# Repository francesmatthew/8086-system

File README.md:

# 8086-system
8086-based system, designed in KiCAD

3D Render of PCB

PCB Overview (fill zones not shown)

Root Sheet

8086 Processor and Bus Demultiplexing Logic

28F010 CMOS Flash

CY7C199 SRAM

8284A Clock Generator

PAL16L8 I/O Address Decoding

8259 Interrupt Controller

8254 Counter

8279 Keyboard

16550 UART Interface

8255 Programmable Peripheral Interface 1

8255 Programmable Peripheral Interface 2

8255 Programmable Peripheral Interface 3

LCD, 7-Segment Displays, LEDs, DIP Switches

Bus Headers, Power Connections

Front Copper Layer

Inner Copper Layer 1

Inner Copper Layer 2

Back Copper Layer

This repository is for submission as the final project for Systems Design and Programming at the University of Maryland, Baltimore County under instruction of William Smith

Unauthorized copying of this project is considered a violation of university academic integrity policy

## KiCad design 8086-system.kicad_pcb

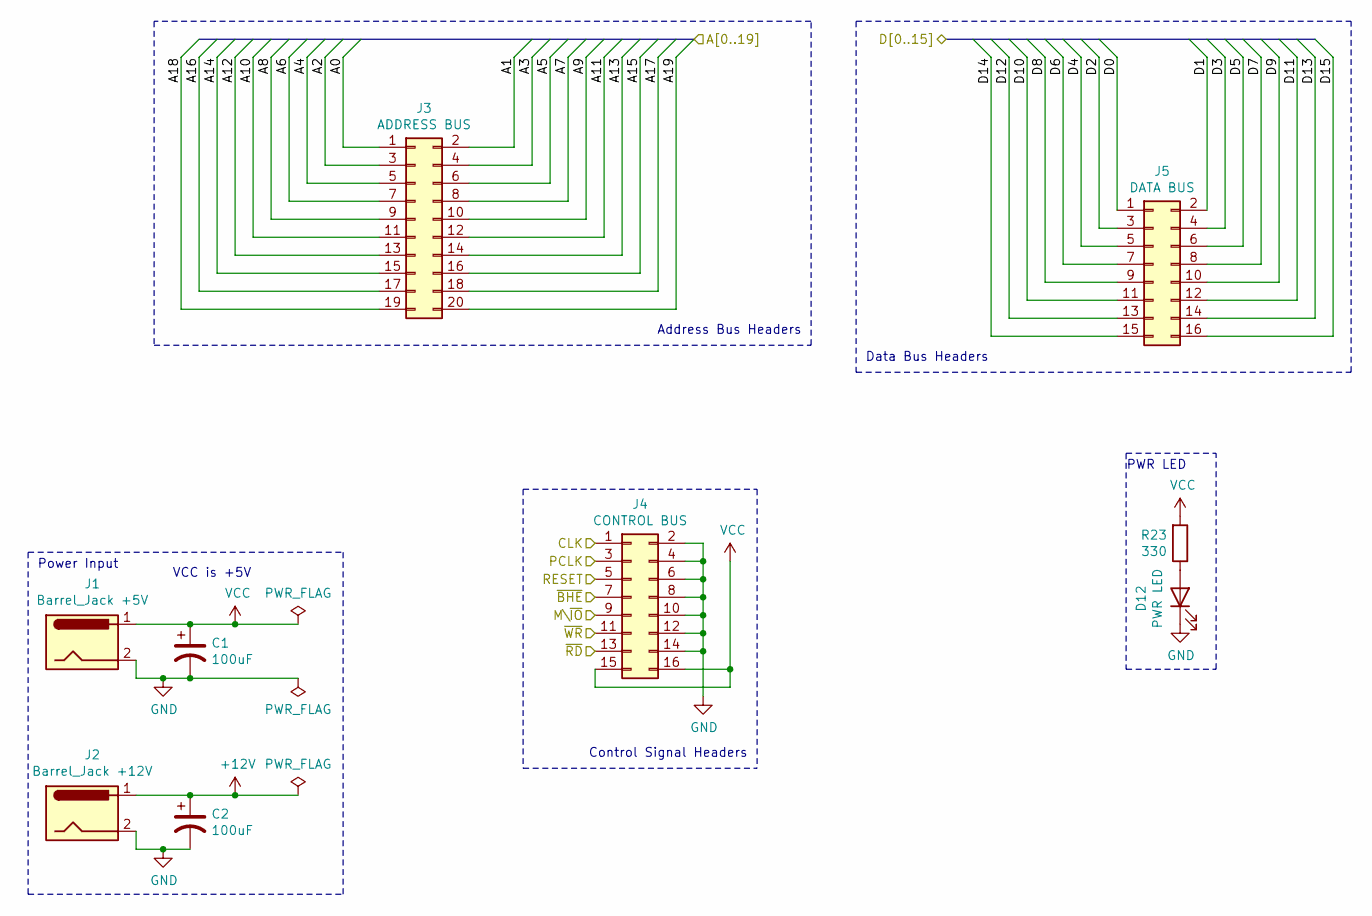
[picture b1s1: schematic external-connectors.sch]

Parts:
C1, C2: 100uF; C_Radial_D6.3mm_H5.0mm_P2.50mm
D12: PWR LED; LED_D5.0mm
J1: Barrel_Jack +5V; BarrelJack_Horizontal
J2: Barrel_Jack +12V; BarrelJack_Horizontal
J3: ADDRESS BUS; PinHeader_2x10_P2.54mm_Vertical
J4: CONTROL BUS; PinHeader_2x08_P2.54mm_Vertical
J5: DATA BUS; PinHeader_2x08_P2.54mm_Vertical
R23: 330; R_Axial_DIN0207_L6.3mm_D2.5mm_P10.16mm_Horizontal

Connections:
+12V: C2.1, J2.1; also elsewhere on the board
/8086-processor/A0: J3.1; also elsewhere on the board
/8086-processor/A1: J3.2; also elsewhere on the board
/8086-processor/A2: J3.3; also elsewhere on the board
/8086-processor/A3: J3.4; also elsewhere on the board
/8086-processor/A4: J3.5; also elsewhere on the board
/8086-processor/A5: J3.6; also elsewhere on the board
/8086-processor/A6: J3.7; also elsewhere on the board
/8086-processor/A7: J3.8; also elsewhere on the board
/8086-processor/A8: J3.9; also elsewhere on the board
/8086-processor/A9: J3.10; also elsewhere on the board
/8086-processor/A10: J3.11; also elsewhere on the board
/8086-processor/A11: J3.12; also elsewhere on the board
/8086-processor/A12: J3.13; also elsewhere on the board
/8086-processor/A13: J3.14; also elsewhere on the board
/8086-processor/A14: J3.15; also elsewhere on the board
/8086-processor/A15: J3.16; also elsewhere on the board
/8086-processor/A16: J3.17; also elsewhere on the board
/8086-processor/A17: J3.18; also elsewhere on the board
/8086-processor/A18: J3.19; also elsewhere on the board
/8086-processor/A19: J3.20; also elsewhere on the board
/8086-processor/D0: J5.1; also elsewhere on the board
/8086-processor/D1: J5.2; also elsewhere on the board
/8086-processor/D2: J5.3; also elsewhere on the board
/8086-processor/D3: J5.4; also elsewhere on the board
/8086-processor/D4: J5.5; also elsewhere on the board
/8086-processor/D5: J5.6; also elsewhere on the board
/8086-processor/D6: J5.7; also elsewhere on the board
/8086-processor/D7: J5.8; also elsewhere on the board
/8086-processor/D8: J5.9; also elsewhere on the board
/8086-processor/D9: J5.10; also elsewhere on the board
/8086-processor/D10: J5.11; also elsewhere on the board
/8086-processor/D11: J5.12; also elsewhere on the board
/8086-processor/D12: J5.13; also elsewhere on the board
/8086-processor/D13: J5.14; also elsewhere on the board
/8086-processor/D14: J5.15; also elsewhere on the board
/8086-processor/D15: J5.16; also elsewhere on the board
/CLK: J4.1; also elsewhere on the board
/M\~IO: J4.9; also elsewhere on the board
/PCLK: J4.3; also elsewhere on the board
/RESET: J4.5; also elsewhere on the board
/~BHE: J4.7; also elsewhere on the board
/~RD: J4.13; also elsewhere on the board
/~WR: J4.11; also elsewhere on the board
GND: C1.2, C2.2, D12.1 (K), J1.2, J2.2, J4.2, J4.4, J4.6, J4.8, J4.10, J4.12, J4.14; also elsewhere on the board
unnamed: D12.2 (A), R23.1
VCC: C1.1, J1.1, J4.15, J4.16, R23.2; also elsewhere on the board

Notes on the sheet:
Data Bus Headers
Address Bus Headers
Power Input
VCC is +5V
Control Signal Headers
PWR LED

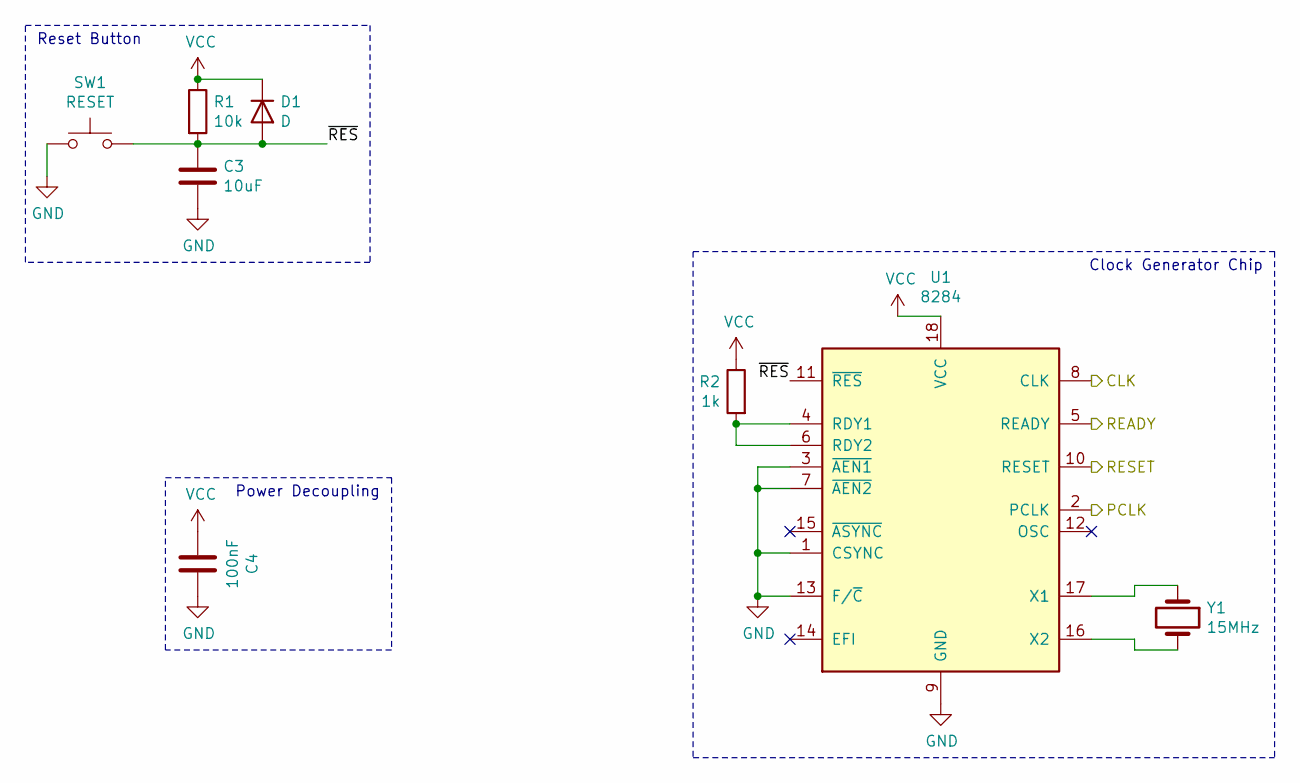
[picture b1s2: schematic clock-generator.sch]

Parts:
C3: 10uF; C_Rect_L4.6mm_W3.8mm_P2.50mm_MKS02_FKP02
C4: 100nF; C_Rect_L4.0mm_W2.5mm_P2.50mm
D1: D; D_DO-35_SOD27_P7.62mm_Horizontal
R1: 10k; R_Axial_DIN0207_L6.3mm_D2.5mm_P10.16mm_Horizontal
R2: 1k; R_Axial_DIN0207_L6.3mm_D2.5mm_P10.16mm_Horizontal
SW1: RESET; SW_Cherry_MX_1.00u_PCB
U1: 8284; DIP-18_W7.62mm
Y1: 15MHz; Crystal_HC49-4H_Vertical

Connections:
/CLK: U1.8 (CLK); also elsewhere on the board
/PCLK: U1.2 (PCLK); also elsewhere on the board
/READY: U1.5 (READY); also elsewhere on the board
/RESET: U1.10 (RESET); also elsewhere on the board
/clock-generator/~RES: C3.1, D1.2 (A), R1.2, SW1.2, U1.11 (~RES~)
GND: C3.2, C4.2, SW1.1, U1.1 (CSYNC), U1.3 (~AEN1~), U1.7 (~AEN2~), U1.9 (GND), U1.13 (F/~C~); also elsewhere on the board
unnamed: R2.2, U1.4 (RDY1), U1.6 (RDY2)
unnamed: U1.16 (X2), Y1.2
unnamed: U1.17 (X1), Y1.1
VCC: C4.1, D1.1 (K), R1.1, R2.1, U1.18 (VCC); also elsewhere on the board

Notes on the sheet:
Clock Generator Chip
Power Decoupling
Reset Button

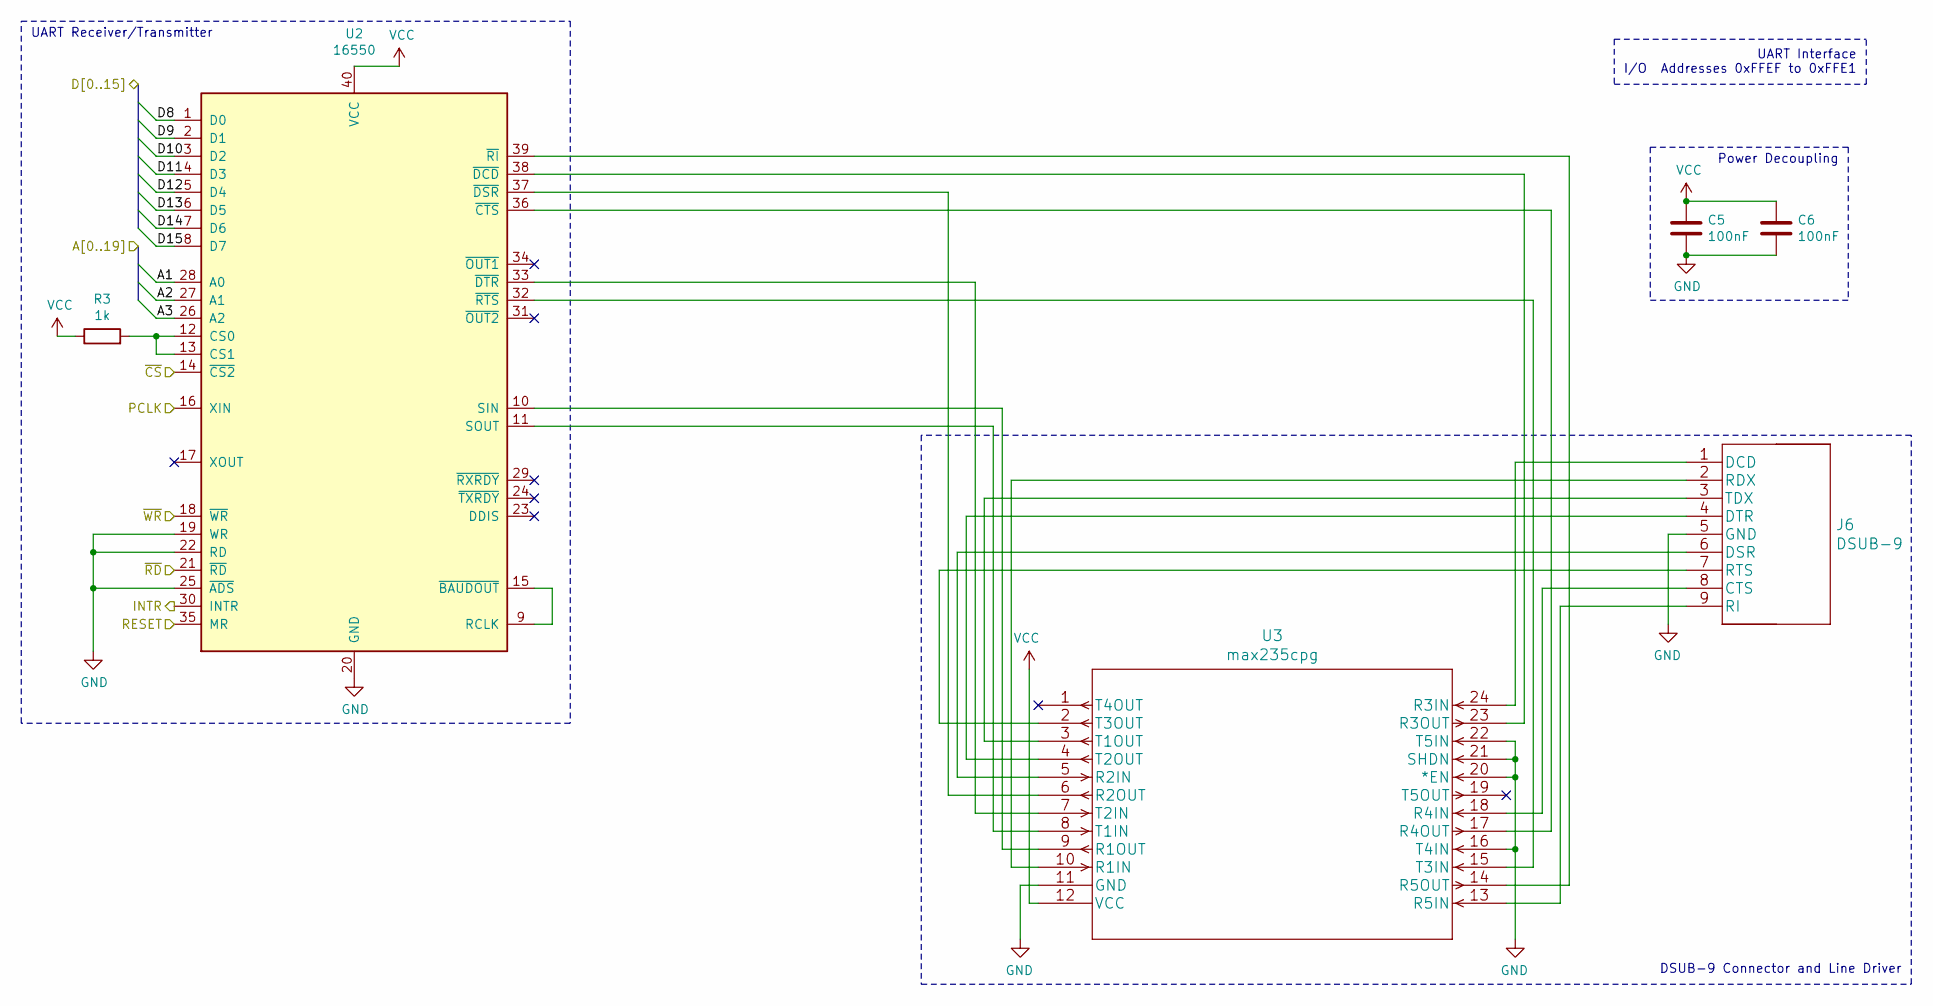
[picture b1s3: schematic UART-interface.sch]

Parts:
C5, C6: 100nF; C_Rect_L4.0mm_W2.5mm_P2.50mm
J6: DSUB-9
R3: 1k; R_Axial_DIN0207_L6.3mm_D2.5mm_P10.16mm_Horizontal
U2: 16550; DIP-40_W15.24mm
U3: max235cpg

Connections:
/8086-processor/A1: U2.28 (A0); also elsewhere on the board
/8086-processor/A2: U2.27 (A1); also elsewhere on the board
/8086-processor/A3: U2.26 (A2); also elsewhere on the board
/8086-processor/D8: U2.1 (D0); also elsewhere on the board
/8086-processor/D9: U2.2 (D1); also elsewhere on the board
/8086-processor/D10: U2.3 (D2); also elsewhere on the board
/8086-processor/D11: U2.4 (D3); also elsewhere on the board
/8086-processor/D12: U2.5 (D4); also elsewhere on the board
/8086-processor/D13: U2.6 (D5); also elsewhere on the board
/8086-processor/D14: U2.7 (D6); also elsewhere on the board
/8086-processor/D15: U2.8 (D7); also elsewhere on the board
/PCLK: U2.16 (XIN); also elsewhere on the board
/RESET: U2.35 (MR); also elsewhere on the board
/UART_INTR: U2.30 (INTR); also elsewhere on the board
/~CS_UART: U2.14 (~CS2~); also elsewhere on the board
/~RD: U2.21 (~RD~); also elsewhere on the board
/~WR: U2.18 (~WR~); also elsewhere on the board
GND: C5.2, C6.2, J6.5 (GND), U2.19 (WR), U2.20 (GND), U2.22 (RD), U2.25 (~ADS~), U3.11 (GND), U3.16 (T4IN), U3.20 (*EN), U3.21 (SHDN), U3.22 (T5IN); also elsewhere on the board
unnamed: J6.1 (DCD), U3.24 (R3IN)
unnamed: J6.2 (RDX), U3.10 (R1IN)
unnamed: J6.3 (TDX), U3.3 (T1OUT)
unnamed: J6.4 (DTR), U3.4 (T2OUT)
unnamed: J6.6 (DSR), U3.5 (R2IN)
unnamed: J6.7 (RTS), U3.2 (T3OUT)
unnamed: J6.8 (CTS), U3.18 (R4IN)
unnamed: J6.9 (RI), U3.13 (R5IN)
unnamed: R3.2, U2.12 (CS0), U2.13 (CS1)
unnamed: U2.10 (SIN), U3.9 (R1OUT)
unnamed: U2.11 (SOUT), U3.8 (T1IN)
unnamed: U2.9 (RCLK), U2.15 (~BAUDOUT~)
unnamed: U2.32 (~RTS~), U3.15 (T3IN)
unnamed: U2.33 (~DTR~), U3.7 (T2IN)
unnamed: U2.36 (~CTS~), U3.17 (R4OUT)
unnamed: U2.37 (~DSR~), U3.6 (R2OUT)
unnamed: U2.38 (~DCD~), U3.23 (R3OUT)
unnamed: U2.39 (~RI~), U3.14 (R5OUT)
VCC: C5.1, C6.1, R3.1, U2.40 (VCC), U3.12 (VCC); also elsewhere on the board

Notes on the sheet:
UART Interface I/O Addresses 0xFFEF to 0xFFE1
UART Receiver/Transmitter
Power Decoupling
DSUB-9 Connector and Line Driver

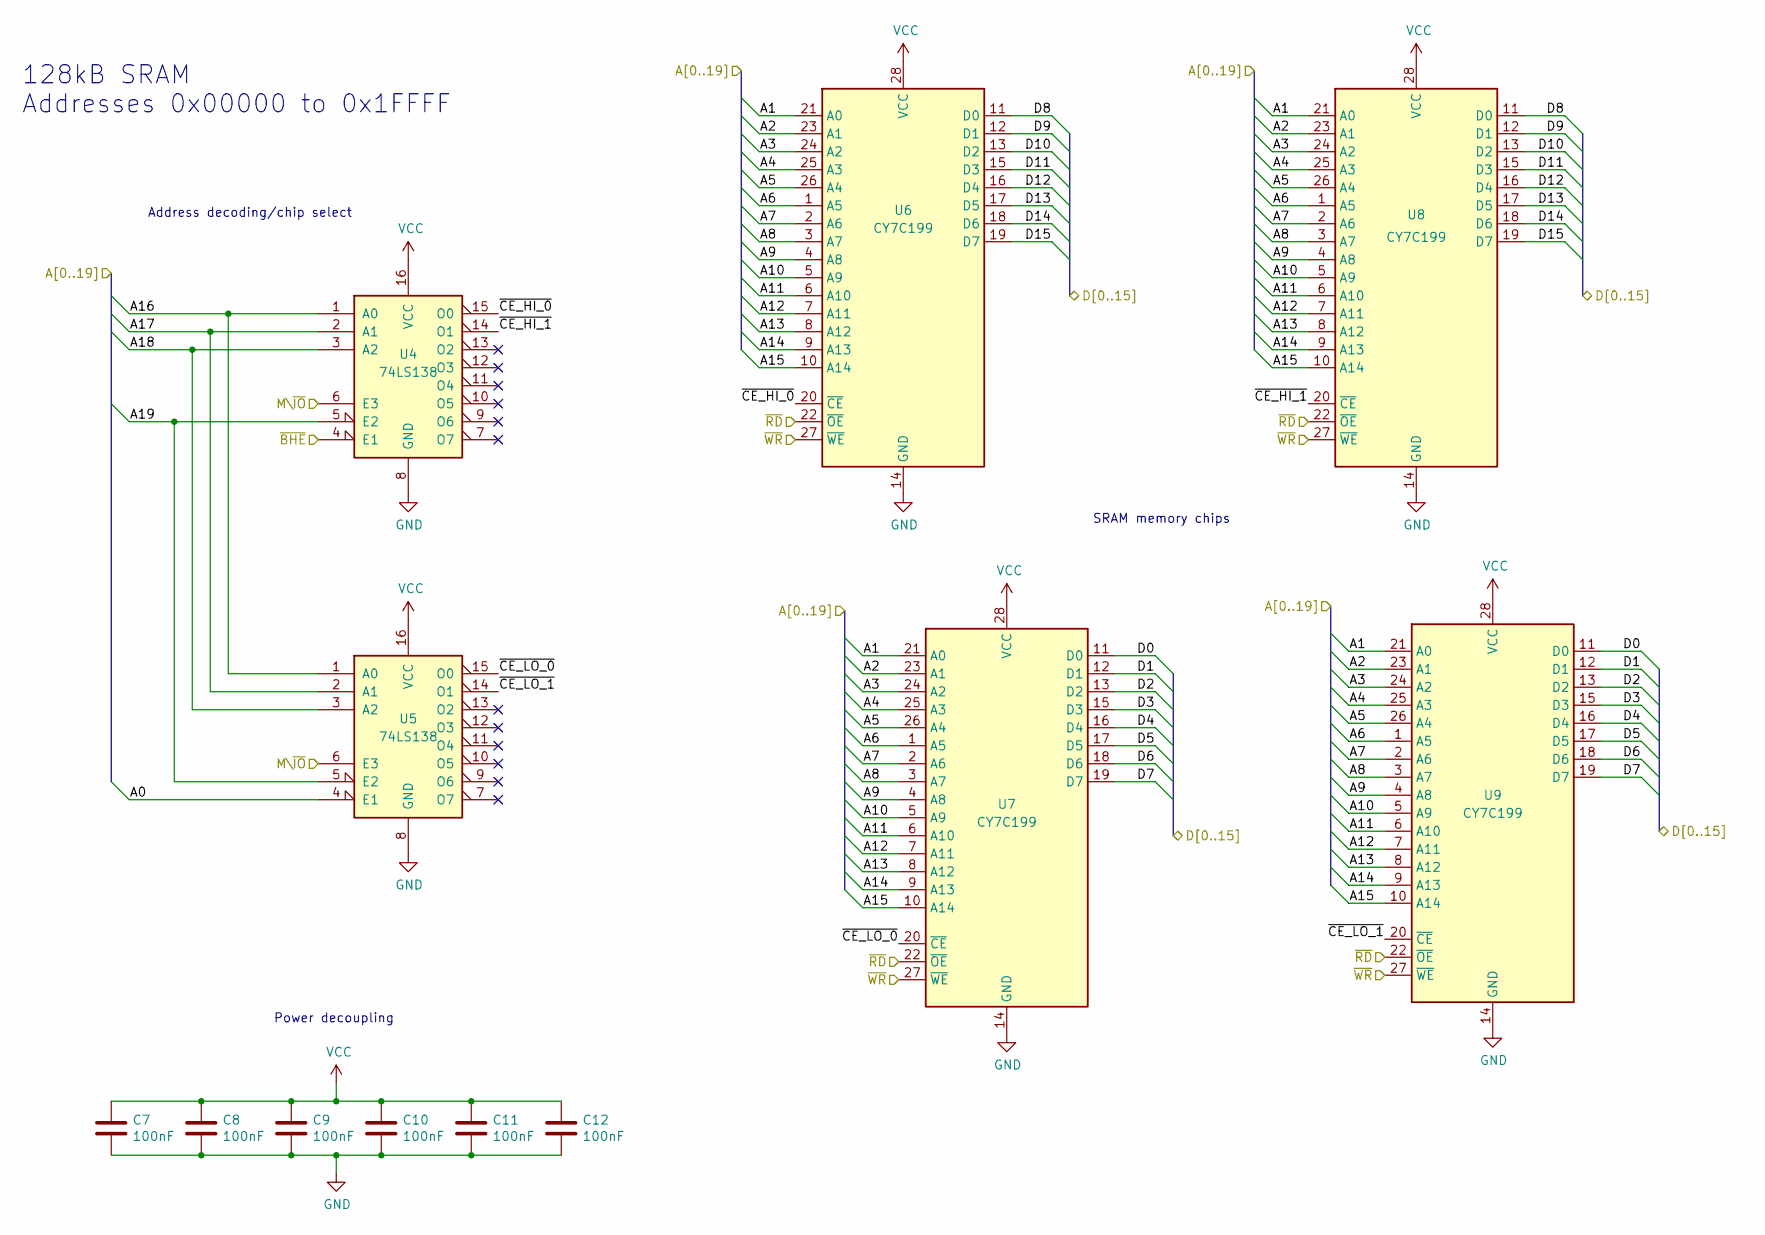
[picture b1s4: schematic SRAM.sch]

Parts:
C7, C8, C9, C10, C11, C12: 100nF; C_Rect_L4.0mm_W2.5mm_P2.50mm
U4, U5: 74LS138; DIP-16_W7.62mm
U6, U7, U8, U9: CY7C199; DIP-28_W7.62mm

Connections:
/8086-processor/A0: U5.4 (E1); also elsewhere on the board
/8086-processor/A1: U6.21 (A0), U7.21 (A0), U8.21 (A0), U9.21 (A0); also elsewhere on the board
/8086-processor/A2: U6.23 (A1), U7.23 (A1), U8.23 (A1), U9.23 (A1); also elsewhere on the board
/8086-processor/A3: U6.24 (A2), U7.24 (A2), U8.24 (A2), U9.24 (A2); also elsewhere on the board
/8086-processor/A4: U6.25 (A3), U7.25 (A3), U8.25 (A3), U9.25 (A3); also elsewhere on the board
/8086-processor/A5: U6.26 (A4), U7.26 (A4), U8.26 (A4), U9.26 (A4); also elsewhere on the board
/8086-processor/A6: U6.1 (A5), U7.1 (A5), U8.1 (A5), U9.1 (A5); also elsewhere on the board
/8086-processor/A7: U6.2 (A6), U7.2 (A6), U8.2 (A6), U9.2 (A6); also elsewhere on the board
/8086-processor/A8: U6.3 (A7), U7.3 (A7), U8.3 (A7), U9.3 (A7); also elsewhere on the board
/8086-processor/A9: U6.4 (A8), U7.4 (A8), U8.4 (A8), U9.4 (A8); also elsewhere on the board
/8086-processor/A10: U6.5 (A9), U7.5 (A9), U8.5 (A9), U9.5 (A9); also elsewhere on the board
/8086-processor/A11: U6.6 (A10), U7.6 (A10), U8.6 (A10), U9.6 (A10); also elsewhere on the board
/8086-processor/A12: U6.7 (A11), U7.7 (A11), U8.7 (A11), U9.7 (A11); also elsewhere on the board
/8086-processor/A13: U6.8 (A12), U7.8 (A12), U8.8 (A12), U9.8 (A12); also elsewhere on the board
/8086-processor/A14: U6.9 (A13), U7.9 (A13), U8.9 (A13), U9.9 (A13); also elsewhere on the board
/8086-processor/A15: U6.10 (A14), U7.10 (A14), U8.10 (A14), U9.10 (A14); also elsewhere on the board
/8086-processor/A16: U4.1 (A0), U5.1 (A0); also elsewhere on the board
/8086-processor/A17: U4.2 (A1), U5.2 (A1); also elsewhere on the board
/8086-processor/A18: U4.3 (A2), U5.3 (A2); also elsewhere on the board
/8086-processor/A19: U4.5 (E2), U5.5 (E2); also elsewhere on the board
/8086-processor/D0: U7.11 (D0), U9.11 (D0); also elsewhere on the board
/8086-processor/D1: U7.12 (D1), U9.12 (D1); also elsewhere on the board
/8086-processor/D2: U7.13 (D2), U9.13 (D2); also elsewhere on the board
/8086-processor/D3: U7.15 (D3), U9.15 (D3); also elsewhere on the board
/8086-processor/D4: U7.16 (D4), U9.16 (D4); also elsewhere on the board
/8086-processor/D5: U7.17 (D5), U9.17 (D5); also elsewhere on the board
/8086-processor/D6: U7.18 (D6), U9.18 (D6); also elsewhere on the board
/8086-processor/D7: U7.19 (D7), U9.19 (D7); also elsewhere on the board
/8086-processor/D8: U6.11 (D0), U8.11 (D0); also elsewhere on the board
/8086-processor/D9: U6.12 (D1), U8.12 (D1); also elsewhere on the board
/8086-processor/D10: U6.13 (D2), U8.13 (D2); also elsewhere on the board
/8086-processor/D11: U6.15 (D3), U8.15 (D3); also elsewhere on the board
/8086-processor/D12: U6.16 (D4), U8.16 (D4); also elsewhere on the board
/8086-processor/D13: U6.17 (D5), U8.17 (D5); also elsewhere on the board
/8086-processor/D14: U6.18 (D6), U8.18 (D6); also elsewhere on the board
/8086-processor/D15: U6.19 (D7), U8.19 (D7); also elsewhere on the board
/M\~IO: U4.6 (E3), U5.6 (E3); also elsewhere on the board
/SRAM/~CE_HI_0: U4.15 (O0), U6.20 (~CE~)
/SRAM/~CE_HI_1: U4.14 (O1), U8.20 (~CE~)
/SRAM/~CE_LO_0: U5.15 (O0), U7.20 (~CE~)
/SRAM/~CE_LO_1: U5.14 (O1), U9.20 (~CE~)
/~BHE: U4.4 (E1); also elsewhere on the board
/~RD: U6.22 (~OE~), U7.22 (~OE~), U8.22 (~OE~), U9.22 (~OE~); also elsewhere on the board
/~WR: U6.27 (~WE~), U7.27 (~WE~), U8.27 (~WE~), U9.27 (~WE~); also elsewhere on the board
GND: C7.2, C8.2, C9.2, C10.2, C11.2, C12.2, U4.8 (GND), U5.8 (GND), U6.14 (GND), U7.14 (GND), U8.14 (GND), U9.14 (GND); also elsewhere on the board
VCC: C7.1, C8.1, C9.1, C10.1, C11.1, C12.1, U4.16 (VCC), U5.16 (VCC), U6.28 (VCC), U7.28 (VCC), U8.28 (VCC), U9.28 (VCC); also elsewhere on the board

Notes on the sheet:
128kB SRAM Addresses 0x00000 to 0x1FFFF
Address decoding/chip select
Power decoupling
SRAM memory chips

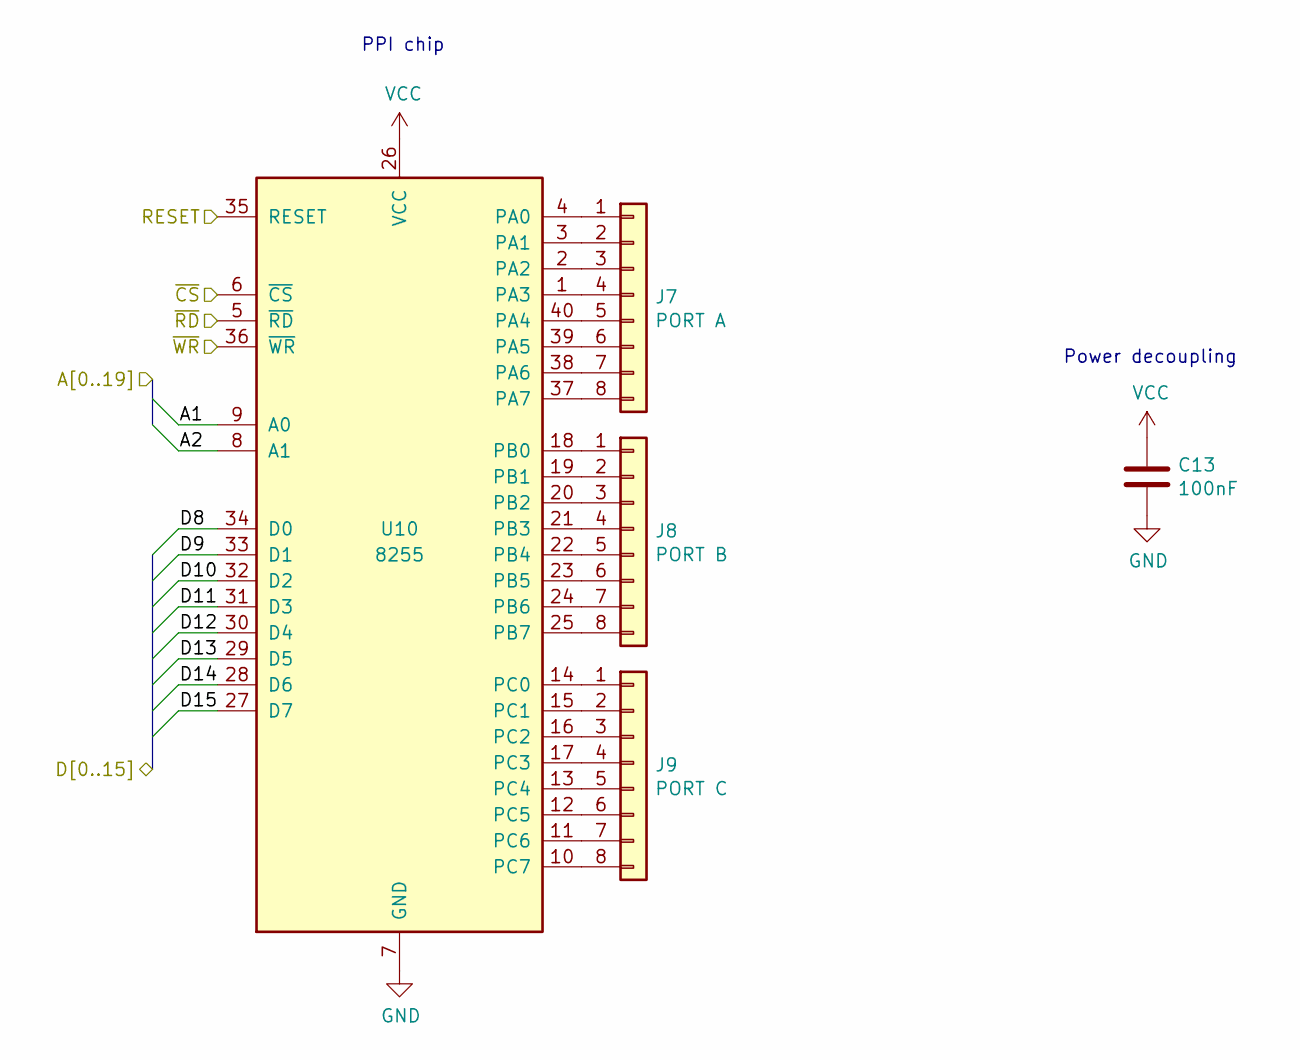
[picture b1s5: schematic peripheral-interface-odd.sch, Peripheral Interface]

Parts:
C13: 100nF; C_Rect_L4.0mm_W2.5mm_P2.50mm
J10: PORT A; PinHeader_1x08_P2.54mm_Vertical
J11: PORT B; PinHeader_1x08_P2.54mm_Vertical
J12: PORT C; PinHeader_1x08_P2.54mm_Vertical
U11: 8255; DIP-40_W15.24mm

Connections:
/8086-processor/A1: U11.9 (A0); also elsewhere on the board
/8086-processor/A2: U11.8 (A1); also elsewhere on the board
/8086-processor/D8: U11.34 (D0); also elsewhere on the board
/8086-processor/D9: U11.33 (D1); also elsewhere on the board
/8086-processor/D10: U11.32 (D2); also elsewhere on the board
/8086-processor/D11: U11.31 (D3); also elsewhere on the board
/8086-processor/D12: U11.30 (D4); also elsewhere on the board
/8086-processor/D13: U11.29 (D5); also elsewhere on the board
/8086-processor/D14: U11.28 (D6); also elsewhere on the board
/8086-processor/D15: U11.27 (D7); also elsewhere on the board
/RESET: U11.35 (RESET); also elsewhere on the board
/~CS_PPI1: U11.6 (~CS~); also elsewhere on the board
/~RD: U11.5 (~RD~); also elsewhere on the board
/~WR: U11.36 (~WR~); also elsewhere on the board
GND: C13.2, U11.7 (GND); also elsewhere on the board
unnamed: J10.1, U11.4 (PA0)
unnamed: J10.2, U11.3 (PA1)
unnamed: J10.3, U11.2 (PA2)
unnamed: J10.4, U11.1 (PA3)
unnamed: J10.5, U11.40 (PA4)
unnamed: J10.6, U11.39 (PA5)
unnamed: J10.7, U11.38 (PA6)
unnamed: J10.8, U11.37 (PA7)
unnamed: J11.1, U11.18 (PB0)
unnamed: J11.2, U11.19 (PB1)
unnamed: J11.3, U11.20 (PB2)
unnamed: J11.4, U11.21 (PB3)
unnamed: J11.5, U11.22 (PB4)
unnamed: J11.6, U11.23 (PB5)
unnamed: J11.7, U11.24 (PB6)
unnamed: J11.8, U11.25 (PB7)
unnamed: J12.1, U11.14 (PC0)
unnamed: J12.2, U11.15 (PC1)
unnamed: J12.3, U11.16 (PC2)
unnamed: J12.4, U11.17 (PC3)
unnamed: J12.5, U11.13 (PC4)
unnamed: J12.6, U11.12 (PC5)
unnamed: J12.7, U11.11 (PC6)
unnamed: J12.8, U11.10 (PC7)
VCC: C13.1, U11.26 (VCC); also elsewhere on the board

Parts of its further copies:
C14: 100nF; C_Rect_L4.0mm_W2.5mm_P2.50mm
J7: PORT A; PinHeader_1x08_P2.54mm_Vertical
J8: PORT B; PinHeader_1x08_P2.54mm_Vertical
J9: PORT C; PinHeader_1x08_P2.54mm_Vertical
U10: 8255; DIP-40_W15.24mm

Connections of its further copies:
/8086-processor/A1: U10.9 (A0); also elsewhere on the board
/8086-processor/A2: U10.8 (A1); also elsewhere on the board
/8086-processor/D8: U10.34 (D0); also elsewhere on the board
/8086-processor/D9: U10.33 (D1); also elsewhere on the board
/8086-processor/D10: U10.32 (D2); also elsewhere on the board
/8086-processor/D11: U10.31 (D3); also elsewhere on the board
/8086-processor/D12: U10.30 (D4); also elsewhere on the board
/8086-processor/D13: U10.29 (D5); also elsewhere on the board
/8086-processor/D14: U10.28 (D6); also elsewhere on the board
/8086-processor/D15: U10.27 (D7); also elsewhere on the board
/RESET: U10.35 (RESET); also elsewhere on the board
/~CS_PPI3: U10.6 (~CS~); also elsewhere on the board
/~RD: U10.5 (~RD~); also elsewhere on the board
/~WR: U10.36 (~WR~); also elsewhere on the board
GND: C14.2, U10.7 (GND); also elsewhere on the board
unnamed: J7.1, U10.4 (PA0)
unnamed: J7.2, U10.3 (PA1)
unnamed: J7.3, U10.2 (PA2)
unnamed: J7.4, U10.1 (PA3)
unnamed: J7.5, U10.40 (PA4)
unnamed: J7.6, U10.39 (PA5)
unnamed: J7.7, U10.38 (PA6)
unnamed: J7.8, U10.37 (PA7)
unnamed: J8.1, U10.18 (PB0)
unnamed: J8.2, U10.19 (PB1)
unnamed: J8.3, U10.20 (PB2)
unnamed: J8.4, U10.21 (PB3)
unnamed: J8.5, U10.22 (PB4)
unnamed: J8.6, U10.23 (PB5)
unnamed: J8.7, U10.24 (PB6)
unnamed: J8.8, U10.25 (PB7)
unnamed: J9.1, U10.14 (PC0)
unnamed: J9.2, U10.15 (PC1)
unnamed: J9.3, U10.16 (PC2)
unnamed: J9.4, U10.17 (PC3)
unnamed: J9.5, U10.13 (PC4)
unnamed: J9.6, U10.12 (PC5)
unnamed: J9.7, U10.11 (PC6)
unnamed: J9.8, U10.10 (PC7)
VCC: C14.1, U10.26 (VCC); also elsewhere on the board

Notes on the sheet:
PPI chip
Power decoupling

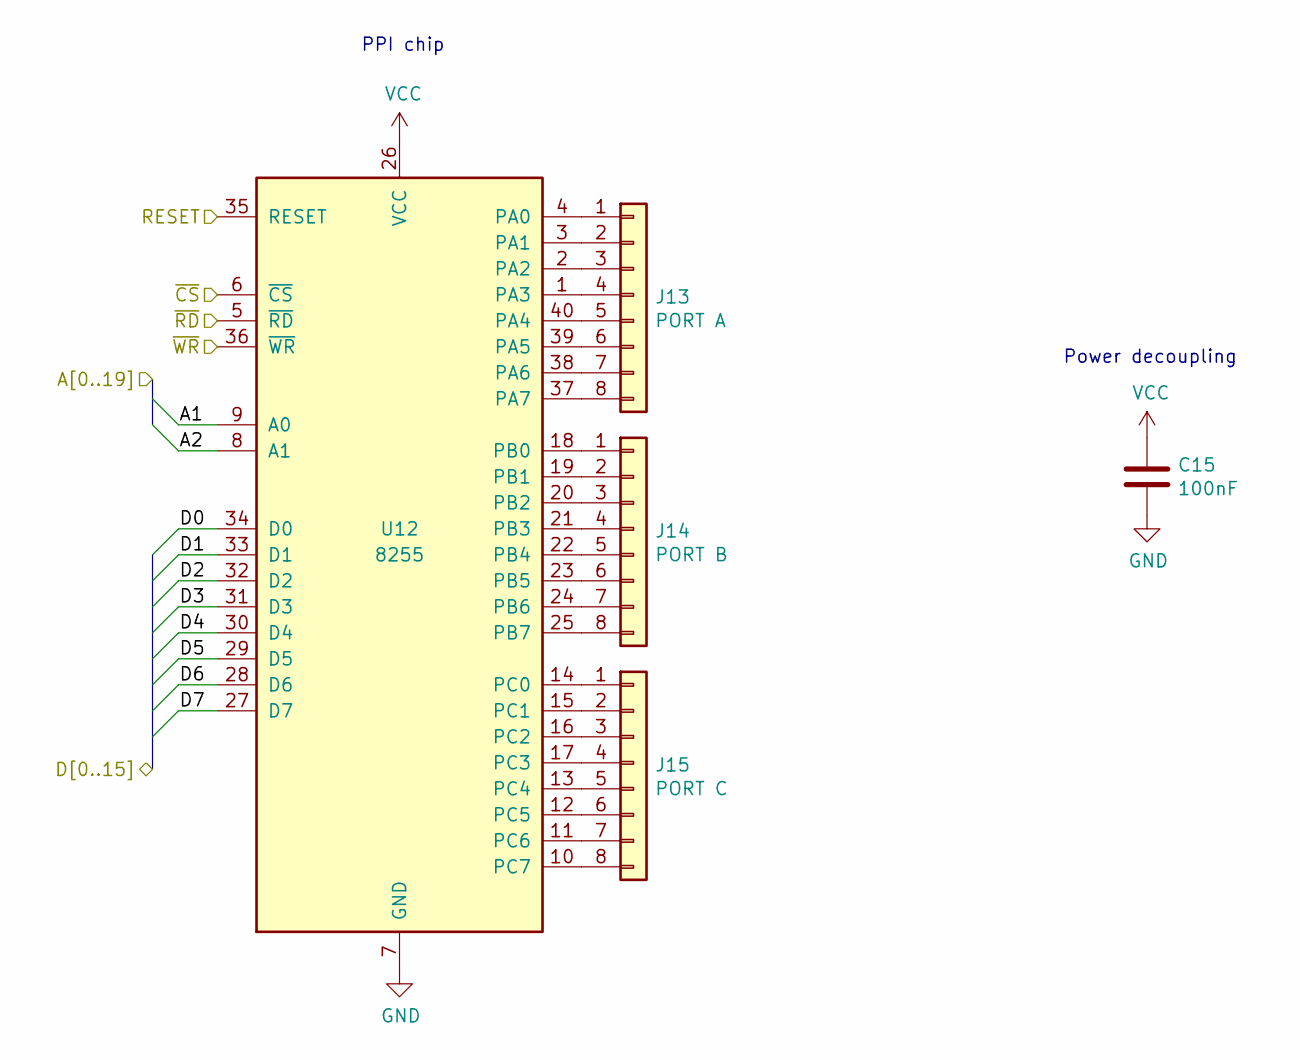
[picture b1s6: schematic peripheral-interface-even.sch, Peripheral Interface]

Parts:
C15: 100nF; C_Rect_L4.0mm_W2.5mm_P2.50mm
J13: PORT A; PinHeader_1x08_P2.54mm_Vertical
J14: PORT B; PinHeader_1x08_P2.54mm_Vertical
J15: PORT C; PinHeader_1x08_P2.54mm_Vertical
U12: 8255; DIP-40_W15.24mm

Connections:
/8086-processor/A1: U12.9 (A0); also elsewhere on the board
/8086-processor/A2: U12.8 (A1); also elsewhere on the board
/8086-processor/D0: U12.34 (D0); also elsewhere on the board
/8086-processor/D1: U12.33 (D1); also elsewhere on the board
/8086-processor/D2: U12.32 (D2); also elsewhere on the board
/8086-processor/D3: U12.31 (D3); also elsewhere on the board
/8086-processor/D4: U12.30 (D4); also elsewhere on the board
/8086-processor/D5: U12.29 (D5); also elsewhere on the board
/8086-processor/D6: U12.28 (D6); also elsewhere on the board
/8086-processor/D7: U12.27 (D7); also elsewhere on the board
/RESET: U12.35 (RESET); also elsewhere on the board
/~CS_PPI2: U12.6 (~CS~); also elsewhere on the board
/~RD: U12.5 (~RD~); also elsewhere on the board
/~WR: U12.36 (~WR~); also elsewhere on the board
GND: C15.2, U12.7 (GND); also elsewhere on the board
unnamed: J13.1, U12.4 (PA0)
unnamed: J13.2, U12.3 (PA1)
unnamed: J13.3, U12.2 (PA2)
unnamed: J13.4, U12.1 (PA3)
unnamed: J13.5, U12.40 (PA4)
unnamed: J13.6, U12.39 (PA5)
unnamed: J13.7, U12.38 (PA6)
unnamed: J13.8, U12.37 (PA7)
unnamed: J14.1, U12.18 (PB0)
unnamed: J14.2, U12.19 (PB1)
unnamed: J14.3, U12.20 (PB2)
unnamed: J14.4, U12.21 (PB3)
unnamed: J14.5, U12.22 (PB4)
unnamed: J14.6, U12.23 (PB5)
unnamed: J14.7, U12.24 (PB6)
unnamed: J14.8, U12.25 (PB7)
unnamed: J15.1, U12.14 (PC0)
unnamed: J15.2, U12.15 (PC1)
unnamed: J15.3, U12.16 (PC2)
unnamed: J15.4, U12.17 (PC3)
unnamed: J15.5, U12.13 (PC4)
unnamed: J15.6, U12.12 (PC5)
unnamed: J15.7, U12.11 (PC6)
unnamed: J15.8, U12.10 (PC7)
VCC: C15.1, U12.26 (VCC); also elsewhere on the board

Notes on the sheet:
PPI chip
Power decoupling

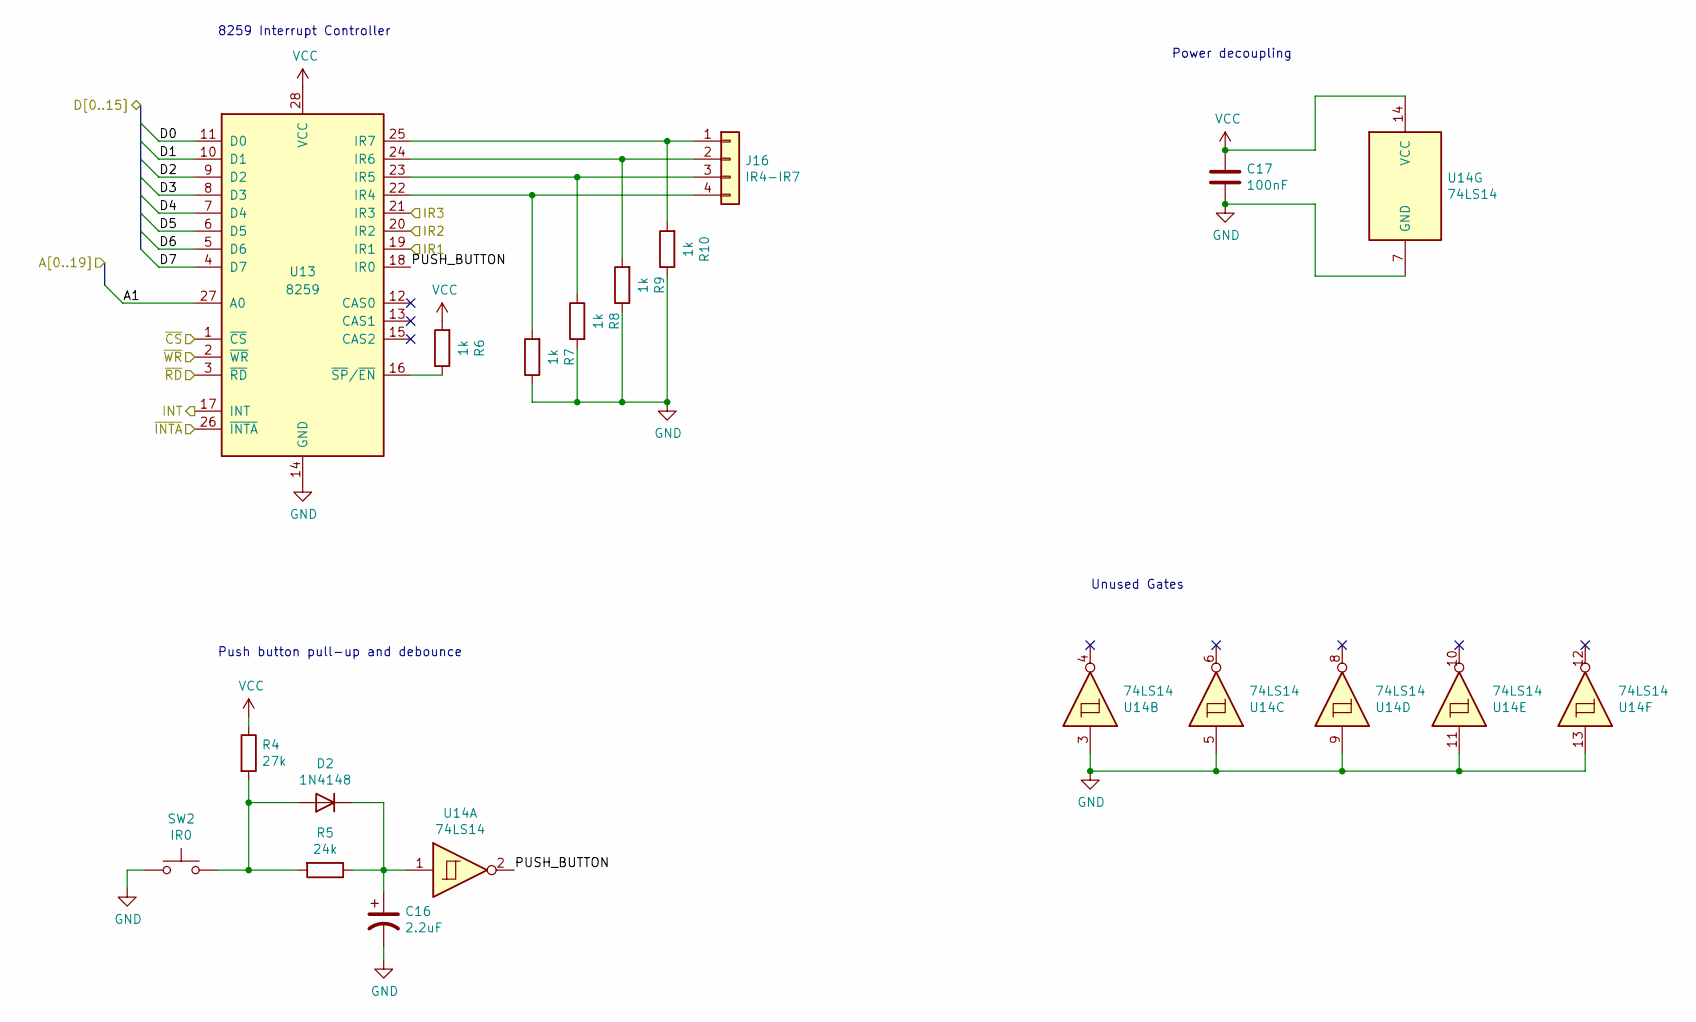
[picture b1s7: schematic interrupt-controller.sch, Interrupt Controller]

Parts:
C16: 2.2uF; CP_Radial_D5.0mm_P2.00mm
C17: 100nF; C_Rect_L4.0mm_W2.5mm_P2.50mm
D2: 1N4148; D_DO-35_SOD27_P7.62mm_Horizontal
J16: IR4-IR7; PinHeader_1x04_P2.54mm_Vertical
R4: 27k; R_Axial_DIN0207_L6.3mm_D2.5mm_P10.16mm_Horizontal
R5: 24k; R_Axial_DIN0207_L6.3mm_D2.5mm_P10.16mm_Horizontal
R6, R7, R8, R9, R10: 1k; R_Axial_DIN0207_L6.3mm_D2.5mm_P10.16mm_Horizontal
SW2: IR0; SW_Cherry_MX_1.00u_PCB
U13: 8259; DIP-28_W15.24mm
U14: 74LS14; DIP-14_W7.62mm

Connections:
/8086-processor/A1: U13.27 (A0); also elsewhere on the board
/8086-processor/D0: U13.11 (D0); also elsewhere on the board
/8086-processor/D1: U13.10 (D1); also elsewhere on the board
/8086-processor/D2: U13.9 (D2); also elsewhere on the board
/8086-processor/D3: U13.8 (D3); also elsewhere on the board
/8086-processor/D4: U13.7 (D4); also elsewhere on the board
/8086-processor/D5: U13.6 (D5); also elsewhere on the board
/8086-processor/D6: U13.5 (D6); also elsewhere on the board
/8086-processor/D7: U13.4 (D7); also elsewhere on the board
/COUNTER_INTR: U13.19 (IR1); also elsewhere on the board
/INTR: U13.17 (INT); also elsewhere on the board
/KEYBOARD_INTR: U13.20 (IR2); also elsewhere on the board
/UART_INTR: U13.21 (IR3); also elsewhere on the board
/interrupt-controller/PUSH_BUTTON: U13.18 (IR0), U14.2
/~CS_INTR: U13.1 (~CS~); also elsewhere on the board
/~INTA: U13.26 (~INTA~); also elsewhere on the board
/~RD: U13.3 (~RD~); also elsewhere on the board
/~WR: U13.2 (~WR~); also elsewhere on the board
GND: C16.2, C17.2, R7.1, R8.2, R9.1, R10.1, SW2.1, U13.14 (GND), U14.3, U14.5, U14.7 (GND), U14.9, U14.11, U14.13; also elsewhere on the board
unnamed: C16.1, D2.1 (K), R5.1, U14.1
unnamed: D2.2 (A), R4.2, R5.2, SW2.2
unnamed: J16.1, R10.2, U13.25 (IR7)
unnamed: J16.2, R9.2, U13.24 (IR6)
unnamed: J16.3, R8.1, U13.23 (IR5)
unnamed: J16.4, R7.2, U13.22 (IR4)
unnamed: R6.1, U13.16 (~SP~/~EN~)
VCC: C17.1, R4.1, R6.2, U13.28 (VCC), U14.14 (VCC); also elsewhere on the board

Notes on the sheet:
Power decoupling
8259 Interrupt Controller
Push button pull-up and debounce
Unused Gates

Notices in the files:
parts and their libraries:
Copyright 2016 Accelerated Designs. All rights reserved.
